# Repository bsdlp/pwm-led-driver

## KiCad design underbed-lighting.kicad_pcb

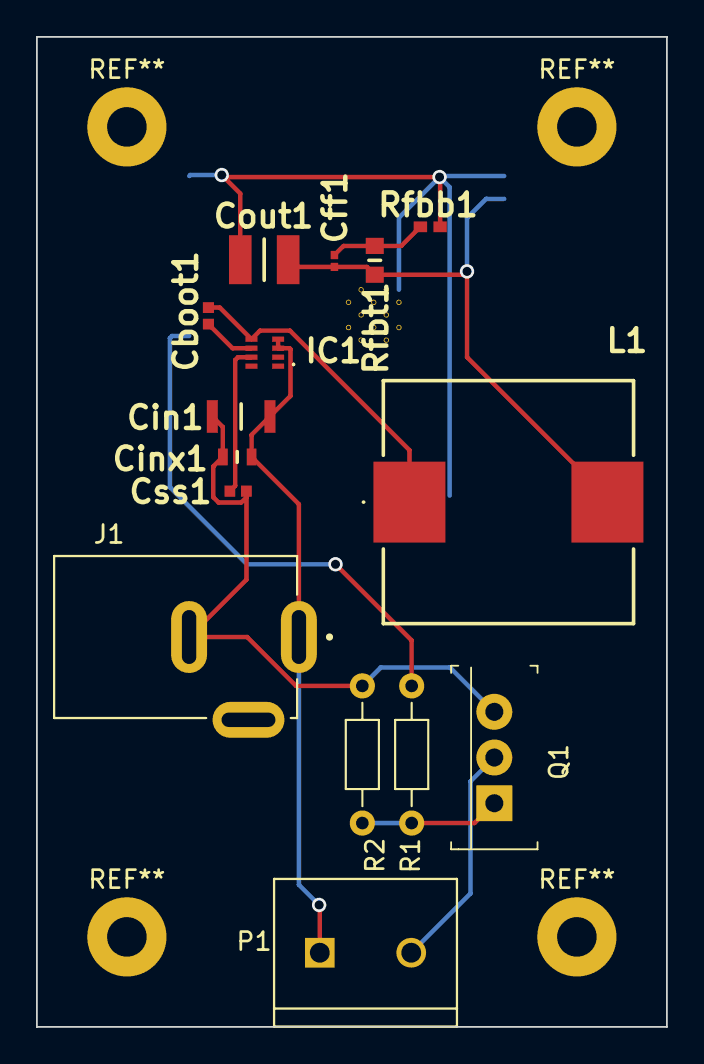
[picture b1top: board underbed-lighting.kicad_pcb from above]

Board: 2 copper layers, 35.0 x 55.0 mm, 16 parts (1 on the bottom side), 10 nets.

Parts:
Cboot1: 100nF; CAPC1005X55N
Cff1: 47pF; CAPC0603X33N
Cin1: 10µF; CAPC3216X180N
Cinx1: 100nF; CAPC1608X90N
Cout1: 47µF; CAPC3225X270N
Css1: 33nF; CAPC1005X55N
IC1: TPS62932DRLR
J1: CON-SOCJ-2155; GRAVITECH_CON-SOCJ-2155
L1: SRP1250-7R8M; SRP12507R8M
P1: 282837-2; TE_282837-2
Q1: IRLB8721PBF; TO-220-3
R1: 1kΩ; R_Axial_DIN0204_L3.6mm_D1.6mm_P7.62mm_Horizontal
R2: 10kΩ; R_Axial_DIN0204_L3.6mm_D1.6mm_P7.62mm_Horizontal
Rfbb1: 10kΩ; RESC1005X40N
Rfbt1: 30.9kΩ; RESC1608X55N
U1: ESP32-WROOM-32E_(16MB); XCVR_ESP32-WROOM-32E_(16MB)

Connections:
GND: Cin1.2, Cinx1.2, Cout1.1, Css1.2, J1.3, Q1.3 (S), R2.2 (-), Rfbb1.1 (+), U1.1 (GND), U1.15 (GND), U1.38 (GND), U1.39_1 (GND), U1.39_2 (GND), U1.39_3 (GND), U1.39_4 (GND), U1.39_5 (GND), U1.39_6 (GND), U1.39_7 (GND), U1.39_8 (GND), U1.39_9 (GND)
unnamed: Cboot1.1, IC1.6 (BST)
unnamed: Cin1.1, Cinx1.1, IC1.3 (VIN), IC1.4 (GND), J1.1, P1.1
unnamed: Css1.1, IC1.7 (SS)
unnamed: Cboot1.2, IC1.5 (SW), L1.1
unnamed: P1.2, Q1.2 (D)
unnamed: Q1.1 (G), R1.2 (-), R2.1 (+)
unnamed: R1.1 (+), U1.31 (IO19)
unnamed: Cff1.1, Rfbb1.2 (-), Rfbt1.1 (+)
unnamed: Cff1.2, Cout1.2, L1.2, Rfbt1.2 (-), U1.2 (3V3)

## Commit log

2023-12-26 design using ti recommended bom
